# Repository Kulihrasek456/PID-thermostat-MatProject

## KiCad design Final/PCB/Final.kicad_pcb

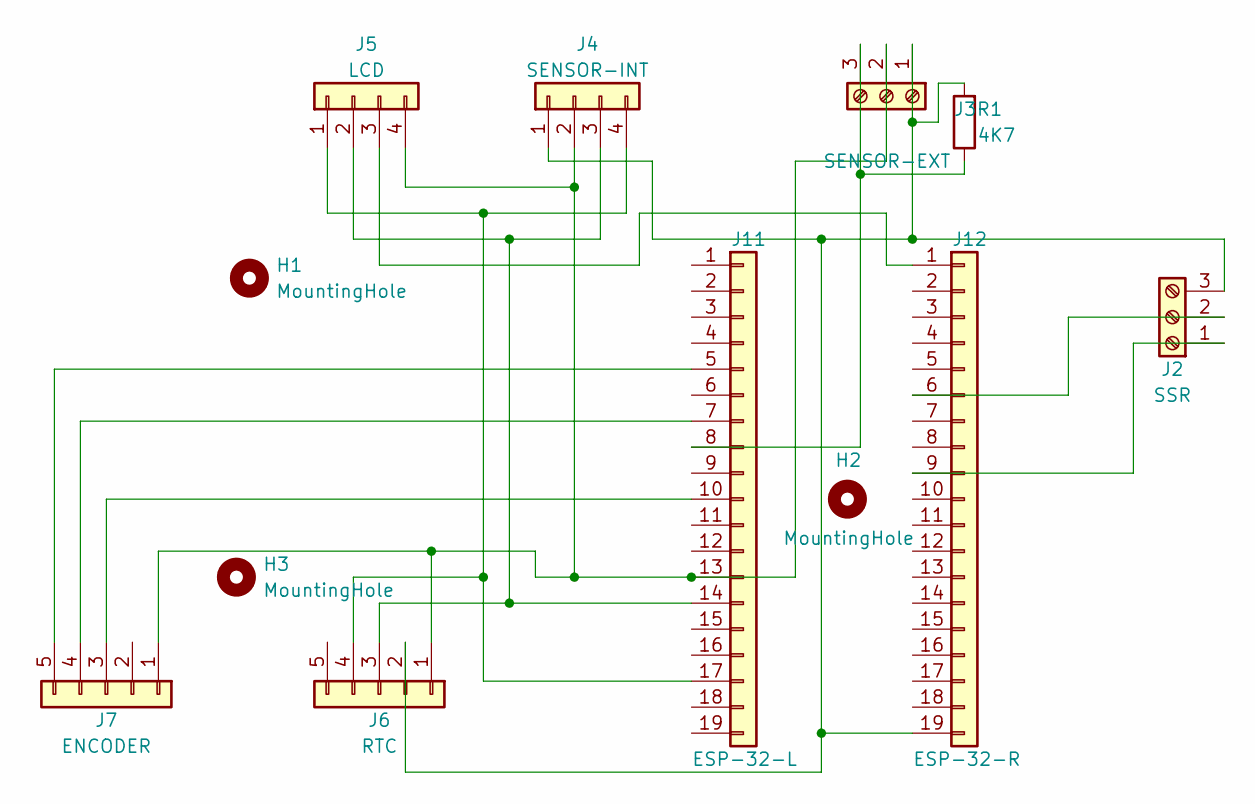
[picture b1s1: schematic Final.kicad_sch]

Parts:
H1, H2, H3: MountingHole; MountingHole_4mm
J2: SSR; TerminalBlock_Phoenix_MKDS-1,5-3_1x03_P5.00mm_Horizontal
J3: SENSOR-EXT; TerminalBlock_Phoenix_MKDS-1,5-3_1x03_P5.00mm_Horizontal
J4: SENSOR-INT; PinHeader_1x04_P2.54mm_Horizontal
J5: LCD; PinHeader_1x04_P2.54mm_Horizontal
J6: RTC; PinHeader_1x05_P2.54mm_Vertical
J7: ENCODER; PinHeader_1x05_P2.54mm_Vertical
J11: ESP-32-L; PinSocket_1x19_P2.54mm_Vertical
J12: ESP-32-R; PinSocket_1x19_P2.54mm_Vertical
R1: 4K7; R_Axial_DIN0411_L9.9mm_D3.6mm_P12.70mm_Horizontal

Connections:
unnamed: J7.5, J11.5 (Pin_GPIO2)
unnamed: J7.4, J11.7 (Pin_GPIO4)
unnamed: J3.3 (Pin_DATA), J11.8 (Pin_GPIO16), R1.1
unnamed: J7.3, J11.10 (Pin_GPIO5)
unnamed: J3.2 (Pin_GND), J4.2, J5.4, J6.1, J7.1, J11.13 (Pin_GND)
unnamed: J4.3, J5.2, J6.3, J11.14 (Pin_SDA)
unnamed: J4.4, J5.1, J6.4, J11.17 (Pin_SCL)
unnamed: J5.3, J12.1
unnamed: J2.2, J12.6 (Pin_GND)
unnamed: J2.1, J12.9 (Pin_GPIO27)
unnamed: J2.3, J3.1 (Pin_VCC), J4.1, J6.2, J12.19 (Pin_3V3), R1.2

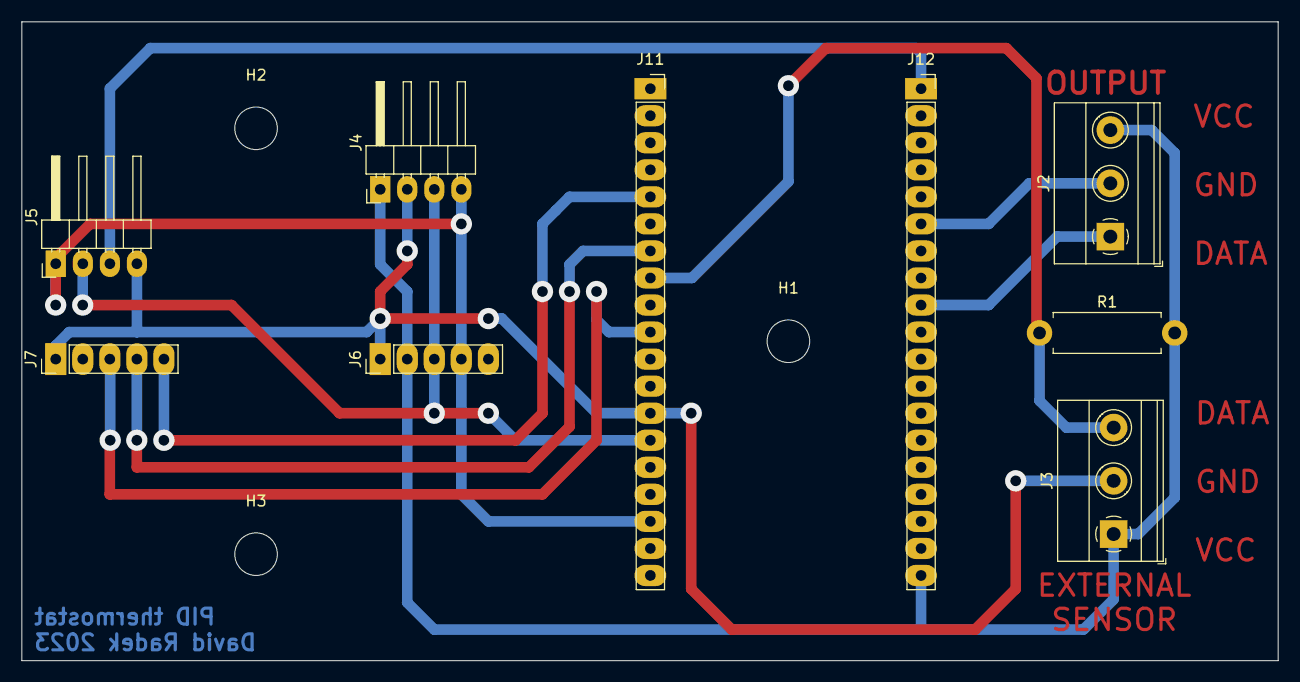
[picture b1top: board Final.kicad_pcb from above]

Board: 2 copper layers, 118.0 x 60.0 mm, 12 parts (0 on the bottom side), 11 nets.

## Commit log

2023-04-15 Nahrání finálních verzí souborů
2023-04-16 final bug fixes
2023-04-16 fix github rep
2023-04-16 Final bug fixes 3
